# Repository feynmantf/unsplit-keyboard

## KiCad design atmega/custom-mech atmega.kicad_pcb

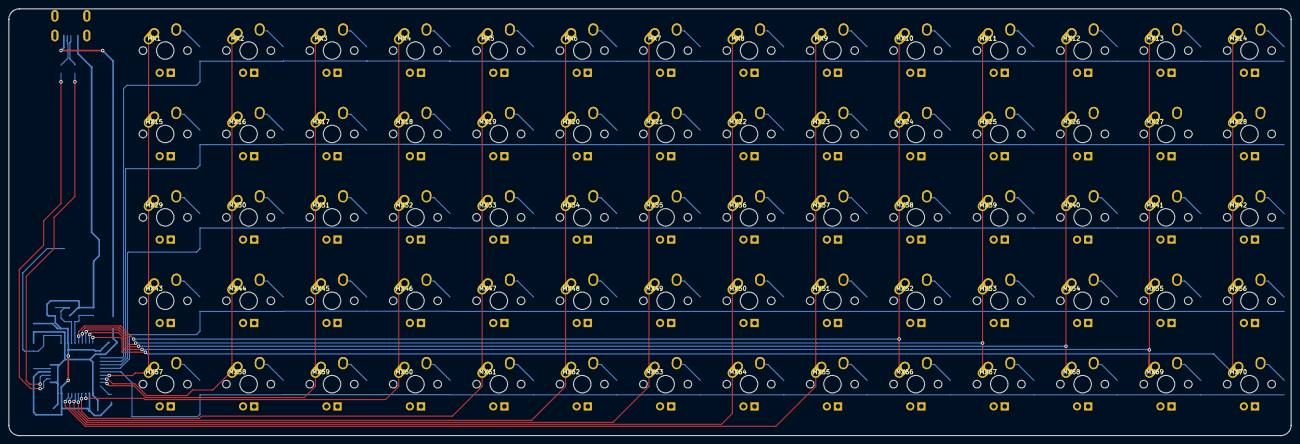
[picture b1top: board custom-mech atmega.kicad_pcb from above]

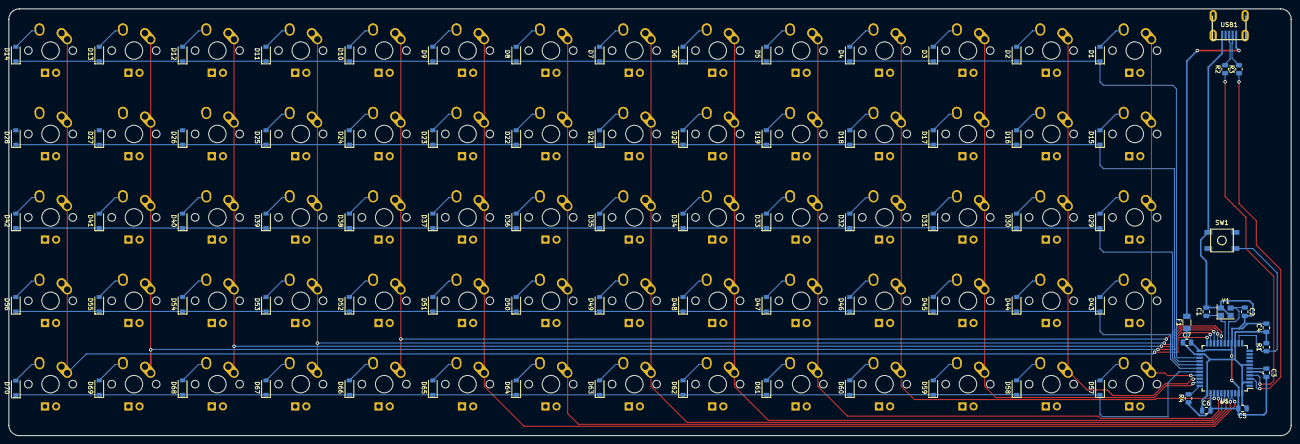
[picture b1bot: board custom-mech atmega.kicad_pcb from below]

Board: 2 copper layers, 292.9 x 97.5 mm, 156 parts (86 on the bottom side), 101 nets.

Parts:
C1, C2: 22pF; C_0805_2012Metric
C3: 1uF; C_0805_2012Metric
C4, C5, C6: 0.1uF; C_0805_2012Metric
C7: 10uF; C_0805_2012Metric
D1, D2, D3, D4, D5, D6, D7, D8, D9, D10, D11, D12, D13, D14, D15, D16, D17, D18, D19, D20, D21, D22, D23, D24, D25, D26, D27, D28, D29, D30, D31, D32, D33, D34, D35, D36, D37, D38, D39, D40, D41, D42, D43, D44, D45, D46, D47, D48, D49, D50, D51, D52, D53, D54, D55, D56, D57, D58, D59, D60, D61, D62, D63, D64, D65, D66, D67, D68, D69, D70: SOD-123; D_SOD-123
F1: 500mA; Fuse_1206_3216Metric
MX1, MX2, MX3, MX4, MX5, MX6, MX7, MX8, MX9, MX10, MX11, MX12, MX13, MX14, MX15, MX16, MX17, MX18, MX19, MX20, MX21, MX22, MX23, MX24, MX25, MX26, MX27, MX28, MX29, MX30, MX31, MX32, MX33, MX34, MX35, MX36, MX37, MX38, MX39, MX40, MX41, MX42, MX43, MX44, MX45, MX46, MX47, MX48, MX49, MX50, MX51, MX52, MX53, MX54, MX55, MX56, MX57, MX58, MX59, MX60, MX61, MX62, MX63, MX64, MX65, MX66, MX67, MX68, MX69, MX70: MX-NoLED; MX-1U
R1, R4: 10k; R_0805_2012Metric
R2, R3: 22; R_0805_2012Metric
SW1: SW_Push; SKQG-1155865
U1: ATmega32U4-AU; TQFP-44_10x10mm_P0.8mm
USB1: Molex-0548190589
Y1: 16MHz; Crystal_SMD_3225-4Pin_3.2x2.5mm

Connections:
+5V: C4.1, C5.1, C6.1, C7.1, F1.1, R1.2, U1.2, U1.7, U1.14, U1.24, U1.34, U1.44
COL0: MX1.1, MX15.1, MX29.1, MX43.1, MX57.1, U1.30
COL1: MX2.1, MX16.1, MX30.1, MX44.1, MX58.1, U1.31
COL2: MX3.1, MX17.1, MX31.1, MX45.1, MX59.1, U1.32
COL3: MX4.1, MX18.1, MX32.1, MX46.1, MX60.1, U1.36
COL4: MX5.1, MX19.1, MX33.1, MX47.1, MX61.1, U1.37
COL5: MX6.1, MX20.1, MX34.1, MX48.1, MX62.1, U1.38
COL6: MX7.1, MX21.1, MX35.1, MX49.1, MX63.1, U1.39
COL7: MX8.1, MX22.1, MX36.1, MX50.1, MX64.1, U1.40
COL8: MX9.1, MX23.1, MX37.1, MX51.1, MX65.1, U1.41
COL9: MX10.1, MX24.1, MX38.1, MX52.1, MX66.1, U1.18
COL10: MX11.1, MX25.1, MX39.1, MX53.1, MX67.1, U1.19
COL11: MX12.1, MX26.1, MX40.1, MX54.1, MX68.1, U1.20
COL12: MX13.1, MX27.1, MX41.1, MX55.1, MX69.1, U1.21
COL13: MX14.1, MX28.1, MX42.1, MX56.1, MX70.1, U1.22
D+: R2.2, USB1.3
D-: R3.2, USB1.4
GND: C1.2, C2.2, C3.2, C4.2, C5.2, C6.2, C7.2, R4.1, SW1.1, U1.5, U1.15, U1.23, U1.35, U1.43, USB1.1, Y1.2, Y1.4
unnamed: C1.1, U1.17, Y1.1
unnamed: C2.1, U1.16, Y1.3
unnamed: C3.1, U1.6
unnamed: D1.2, MX1.2
unnamed: D2.2, MX2.2
unnamed: D3.2, MX3.2
unnamed: D4.2, MX4.2
unnamed: D5.2, MX5.2
unnamed: D6.2, MX6.2
unnamed: D7.2, MX7.2
unnamed: D8.2, MX8.2
unnamed: D9.2, MX9.2
unnamed: D10.2, MX10.2
unnamed: D11.2, MX11.2
unnamed: D12.2, MX12.2
unnamed: D13.2, MX13.2
unnamed: D14.2, MX14.2
unnamed: D15.2, MX15.2
unnamed: D16.2, MX16.2
unnamed: D17.2, MX17.2
unnamed: D18.2, MX18.2
unnamed: D19.2, MX19.2
unnamed: D20.2, MX20.2
unnamed: D21.2, MX21.2
unnamed: D22.2, MX22.2
unnamed: D23.2, MX23.2
unnamed: D24.2, MX24.2
unnamed: D25.2, MX25.2
unnamed: D26.2, MX26.2
unnamed: D27.2, MX27.2
unnamed: D28.2, MX28.2
unnamed: D29.2, MX29.2
unnamed: D30.2, MX30.2
unnamed: D31.2, MX31.2
unnamed: D32.2, MX32.2
unnamed: D33.2, MX33.2
unnamed: D34.2, MX34.2
unnamed: D35.2, MX35.2
unnamed: D36.2, MX36.2
unnamed: D37.2, MX37.2
unnamed: D38.2, MX38.2
unnamed: D39.2, MX39.2
unnamed: D40.2, MX40.2
unnamed: D41.2, MX41.2
unnamed: D42.2, MX42.2
unnamed: D43.2, MX43.2
unnamed: D44.2, MX44.2
unnamed: D45.2, MX45.2
unnamed: D46.2, MX46.2
unnamed: D47.2, MX47.2
unnamed: D48.2, MX48.2
unnamed: D49.2, MX49.2
unnamed: D50.2, MX50.2
unnamed: D51.2, MX51.2
unnamed: D52.2, MX52.2
unnamed: D53.2, MX53.2
unnamed: D54.2, MX54.2
unnamed: D55.2, MX55.2
unnamed: D56.2, MX56.2
unnamed: D57.2, MX57.2
unnamed: D58.2, MX58.2
unnamed: D59.2, MX59.2
unnamed: D60.2, MX60.2
unnamed: D61.2, MX61.2
unnamed: D62.2, MX62.2
unnamed: D63.2, MX63.2
unnamed: D64.2, MX64.2
unnamed: D65.2, MX65.2
unnamed: D66.2, MX66.2
unnamed: D67.2, MX67.2
unnamed: D68.2, MX68.2
unnamed: D69.2, MX69.2
unnamed: D70.2, MX70.2
unnamed: R1.1, SW1.2, U1.13
unnamed: R2.1, U1.4
unnamed: R3.1, U1.3
unnamed: R4.2, U1.33
ROW0: D1.1, D2.1, D3.1, D4.1, D5.1, D6.1, D7.1, D8.1, D9.1, D10.1, D11.1, D12.1, D13.1, D14.1, U1.25
ROW1: D15.1, D16.1, D17.1, D18.1, D19.1, D20.1, D21.1, D22.1, D23.1, D24.1, D25.1, D26.1, D27.1, D28.1, U1.26
ROW2: D29.1, D30.1, D31.1, D32.1, D33.1, D34.1, D35.1, D36.1, D37.1, D38.1, D39.1, D40.1, D41.1, D42.1, U1.27
ROW3: D43.1, D44.1, D45.1, D46.1, D47.1, D48.1, D49.1, D50.1, D51.1, D52.1, D53.1, D54.1, D55.1, D56.1, U1.28
ROW4: D57.1, D58.1, D59.1, D60.1, D61.1, D62.1, D63.1, D64.1, D65.1, D66.1, D67.1, D68.1, D69.1, D70.1, U1.29
VCC: F1.2, USB1.5

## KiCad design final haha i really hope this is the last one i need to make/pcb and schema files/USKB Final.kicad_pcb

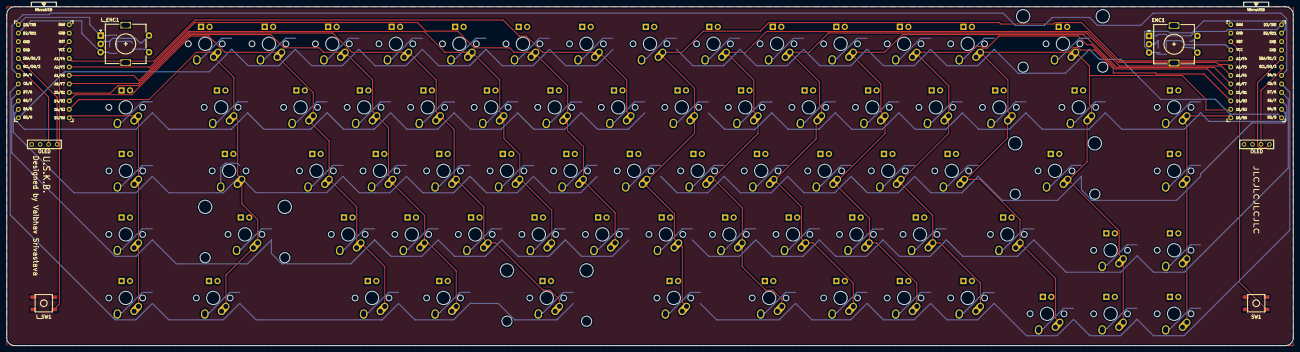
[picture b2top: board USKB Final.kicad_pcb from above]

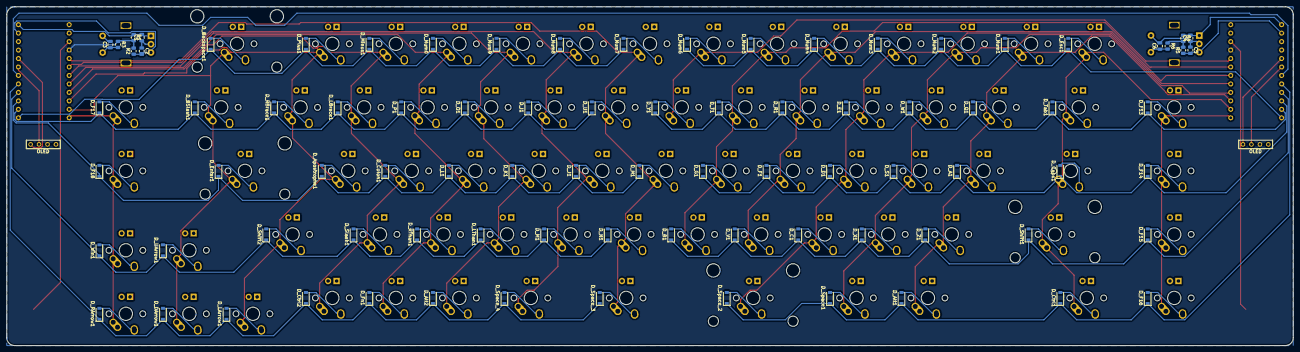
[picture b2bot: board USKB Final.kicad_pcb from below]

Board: 2 copper layers, 385.8 x 101.6 mm, 166 parts (85 on the bottom side), 114 nets.

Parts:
C1, C2, C3, C4, C5, C6: 0.1u; C_0805_2012Metric
D_A1: SMD_123; D_SOD-123
D_Alt1, D_Alt2: SMD_123; D_SOD-123
D_Apostrophe1: SMD_123; D_SOD-123
D_B1: SMD_123; D_SOD-123
D_BSlash1: SMD_123; D_SOD-123
D_Backspace1: SMD_123; D_SOD-123
D_C1: SMD_123; D_SOD-123
D_Caps1: SMD_123; D_SOD-123
D_Colon1: SMD_123; D_SOD-123
D_Ctrl1, D_Ctrl2: SMD_123; D_SOD-123
D_D1: SMD_123; D_SOD-123
D_DArrow1: SMD_123; D_SOD-123
D_E1: SMD_123; D_SOD-123
D_Enter1: SMD_123; D_SOD-123
D_Esc1: SMD_123; D_SOD-123
D_F1, D_F13, D_F14, D_F15, D_F16, D_F17, D_F18: SMD_123; D_SOD-123
D_Fn1: SMD_123; D_SOD-123
D_G1: SMD_123; D_SOD-123
D_H1: SMD_123; D_SOD-123
D_I1: SMD_123; D_SOD-123
D_J1: SMD_123; D_SOD-123
D_K1: SMD_123; D_SOD-123
D_L1: SMD_123; D_SOD-123
D_LArrow1: SMD_123; D_SOD-123
D_LBrace1: SMD_123; D_SOD-123
D_LThan1: SMD_123; D_SOD-123
D_M1: SMD_123; D_SOD-123
D_Minus1: SMD_123; D_SOD-123
D_N1: SMD_123; D_SOD-123
D_Num0, D_Num1, D_Num2, D_Num3, D_Num4, D_Num5, D_Num6, D_Num7, D_Num8, D_Num9: SMD_123; D_SOD-123
D_O1: SMD_123; D_SOD-123
D_P1: SMD_123; D_SOD-123
D_Plus1: SMD_123; D_SOD-123
D_Q1: SMD_123; D_SOD-123
D_R1: SMD_123; D_SOD-123
D_RArrow1: SMD_123; D_SOD-123
D_RBrace1: SMD_123; D_SOD-123
D_RThan1: SMD_123; D_SOD-123
D_S1: SMD_123; D_SOD-123
D_Shift1, D_Shift2: SMD_123; D_SOD-123
D_Slash1: SMD_123; D_SOD-123
D_Space1: SMD_123; D_SOD-123
D_Space_2, D_Space_3, D_Space_4: SMD_123; D_SOD-123
D_T1: SMD_123; D_SOD-123
D_Tab1: SMD_123; D_SOD-123
D_U1: SMD_123; D_SOD-123
D_UArrow1: SMD_123; D_SOD-123
D_V1: SMD_123; D_SOD-123
D_W1: SMD_123; D_SOD-123
D_Win1: SMD_123; D_SOD-123
D_X1: SMD_123; D_SOD-123
D_Y1: SMD_123; D_SOD-123
D_Z1: SMD_123; D_SOD-123
ENC1: Rotary_Encoder_Switch; RotaryEncoder_Alps_EC11E-Switch_Vertical_H20mm
K_A1: MX-NoLED; MX-1U
K_Alt1: MX-NoLED; MX-1.25U
K_Alt2: MX-NoLED; MX-1U
K_Apostrophe1: MX-NoLED; MX-1U
K_B1: MX-NoLED; MX-1U
K_BSlash1: MX-NoLED; MX-1.5U
K_Backspace1: MX-NoLED; MX-2U
K_C1: MX-NoLED; MX-1U
K_Caps1: MX-NoLED; MX-1.75U
K_Colon1: MX-NoLED; MX-1U
K_Ctrl1: MX-NoLED; MX-1.25U
K_Ctrl2: MX-NoLED; MX-1U
K_D1: MX-NoLED; MX-1U
K_DArrow1: MX-NoLED; MX-1U
K_E1: MX-NoLED; MX-1U
K_Enter1: MX-NoLED; MX-2.25U
K_Esc1: MX-NoLED; MX-1U
K_F1, K_F13, K_F14, K_F15, K_F16, K_F17, K_F18: MX-NoLED; MX-1U
K_Fn1: MX-NoLED; MX-1U
K_G1: MX-NoLED; MX-1U
K_H1: MX-NoLED; MX-1U
K_I1: MX-NoLED; MX-1U
K_J1: MX-NoLED; MX-1U
K_K1: MX-NoLED; MX-1U
K_L1: MX-NoLED; MX-1U
K_LArrow1: MX-NoLED; MX-1U
K_LBrace1: MX-NoLED; MX-1U
K_LThan1: MX-NoLED; MX-1U
K_M1: MX-NoLED; MX-1U
K_Minus1: MX-NoLED; MX-1U
K_N1: MX-NoLED; MX-1U
K_Num0, K_Num1, K_Num2, K_Num3, K_Num4, K_Num5, K_Num6, K_Num7, K_Num8, K_Num9: MX-NoLED; MX-1U
K_O1: MX-NoLED; MX-1U
K_P1: MX-NoLED; MX-1U
K_Plus1: MX-NoLED; MX-1U
K_Q1: MX-NoLED; MX-1U
K_R1: MX-NoLED; MX-1U
K_RArrow1: MX-NoLED; MX-1U
K_RBrace1: MX-NoLED; MX-1U
K_RThan1: MX-NoLED; MX-1U
K_S1: MX-NoLED; MX-1U
K_Shift1: MX-NoLED; MX-2.25U
K_Shift2: MX-NoLED; MX-1.75U
K_Slash1: MX-NoLED; MX-1U
K_Space1: MX-NoLED; MX-1U
K_Space_2: MX-NoLED; MX-2.25U
K_Space_3: MX-NoLED; MX-1.75U
K_Space_4: MX-NoLED; MX-1.25U
K_T1: MX-NoLED; MX-1U
K_Tab1: MX-NoLED; MX-1.5U
K_U1: MX-NoLED; MX-1U
K_UArrow1: MX-NoLED; MX-1U
K_V1: MX-NoLED; MX-1U
K_W1: MX-NoLED; MX-1U
K_Win1: MX-NoLED; MX-1U
K_X1: MX-NoLED; MX-1U
K_Y1: MX-NoLED; MX-1U
K_Z1: MX-NoLED; MX-1U
L_ENC1: Rotary_Encoder_Switch; RotaryEncoder_Alps_EC11E-Switch_Vertical_H20mm
L_OL1: OLED
L_SW1: SW_PUSH; SKQG-1155865
L_U1: ProMicro; ProMicro_v3
OL1: OLED
R1, R2, R3, R4, R5, R6: 10k; R_0805_2012Metric
SW1: SW_PUSH; SKQG-1155865
U1: ProMicro; ProMicro_v3

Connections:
COL0: K_H1.1, K_N1.1, K_Num7.1, K_Space_3.1, K_U1.1, U1.20
COL1: K_I1.1, K_J1.1, K_M1.1, K_Num8.1, K_Space_4.1, U1.19
COL2: K_Alt2.1, K_K1.1, K_LThan1.1, K_Num9.1, K_O1.1, U1.18
COL3: K_Fn1.1, K_L1.1, K_Num0.1, K_P1.1, K_RThan1.1, U1.17
COL4: K_Colon1.1, K_Ctrl2.1, K_LBrace1.1, K_Minus1.1, K_Slash1.1, U1.16
COL5: K_Apostrophe1.1, K_LArrow1.1, K_Plus1.1, K_RBrace1.1, K_Shift2.1, U1.15
COL6: K_BSlash1.1, K_Backspace1.1, K_DArrow1.1, K_Enter1.1, K_UArrow1.1, U1.14
COL7: K_F17.1, K_F18.1, K_RArrow1.1, K_Win1.1, U1.13
DATA: L_U1.7, U1.7
GND: C1.1, C2.1, C3.2, C4.1, C5.1, C6.2, ENC1.C, ENC1.S2, L_ENC1.C, L_ENC1.S2, L_OL1.4, L_SW1.2, L_U1.3, L_U1.4, L_U1.23, OL1.4, SW1.2, U1.3, U1.4, U1.23
K_ENC: C3.1, ENC1.S1, R3.2
L_COL0: K_F13.1, K_F14.1, K_F15.1, K_F16.1, L_U1.13
L_COL1: K_Caps1.1, K_Ctrl1.1, K_Esc1.1, K_Shift1.1, K_Tab1.1, L_U1.14
L_COL2: K_A1.1, K_Alt1.1, K_Num1.1, K_Q1.1, K_Z1.1, L_U1.15
L_COL3: K_Num2.1, K_S1.1, K_Space1.1, K_W1.1, K_X1.1, L_U1.16
L_COL4: K_C1.1, K_D1.1, K_E1.1, K_Num3.1, K_Space_2.1, L_U1.17
L_COL5: K_F1.1, K_Num4.1, K_R1.1, K_V1.1, L_U1.18
L_COL6: K_B1.1, K_G1.1, K_Num5.1, K_T1.1, L_U1.19
L_COL7: K_Num6.1, K_Y1.1, L_U1.20
L_K_ENC: C6.1, L_ENC1.S1, R6.2
L_RESET: L_SW1.1, L_U1.22
L_ROT_A: C4.2, L_ENC1.A, L_U1.1, R4.1
L_ROT_B: C5.2, L_ENC1.B, L_U1.2, R5.1
L_ROW0: D_Esc1.1, D_Num1.1, D_Num2.1, D_Num3.1, D_Num4.1, D_Num5.1, D_Num6.1, L_U1.12
L_ROW1: D_E1.1, D_F13.1, D_Q1.1, D_R1.1, D_T1.1, D_Tab1.1, D_W1.1, D_Y1.1, L_U1.11
L_ROW2: D_A1.1, D_Caps1.1, D_D1.1, D_F1.1, D_F14.1, D_G1.1, D_S1.1, L_U1.10
L_ROW3: D_B1.1, D_C1.1, D_F15.1, D_Shift1.1, D_V1.1, D_X1.1, D_Z1.1, L_U1.9
L_ROW4: D_Alt1.1, D_Ctrl1.1, D_F16.1, D_Space1.1, D_Space_2.1, L_U1.8
L_SCL: L_OL1.2, L_U1.6
L_SDA: L_OL1.1, L_U1.5
unnamed: D_A1.2, K_A1.2
unnamed: D_Alt1.2, K_Alt1.2
unnamed: D_Alt2.2, K_Alt2.2
unnamed: D_Apostrophe1.2, K_Apostrophe1.2
unnamed: D_B1.2, K_B1.2
unnamed: D_BSlash1.2, K_BSlash1.2
unnamed: D_Backspace1.2, K_Backspace1.2
unnamed: D_C1.2, K_C1.2
unnamed: D_Caps1.2, K_Caps1.2
unnamed: D_Colon1.2, K_Colon1.2
unnamed: D_Ctrl1.2, K_Ctrl1.2
unnamed: D_Ctrl2.2, K_Ctrl2.2
unnamed: D_D1.2, K_D1.2
unnamed: D_DArrow1.2, K_DArrow1.2
unnamed: D_E1.2, K_E1.2
unnamed: D_Enter1.2, K_Enter1.2
unnamed: D_Esc1.2, K_Esc1.2
unnamed: D_F1.2, K_F1.2
unnamed: D_F13.2, K_F13.2
unnamed: D_F14.2, K_F14.2
unnamed: D_F15.2, K_F15.2
unnamed: D_F16.2, K_F16.2
unnamed: D_F17.2, K_F17.2
unnamed: D_F18.2, K_F18.2
unnamed: D_Fn1.2, K_Fn1.2
unnamed: D_G1.2, K_G1.2
unnamed: D_H1.2, K_H1.2
unnamed: D_I1.2, K_I1.2
unnamed: D_J1.2, K_J1.2
unnamed: D_K1.2, K_K1.2
unnamed: D_L1.2, K_L1.2
unnamed: D_LArrow1.2, K_LArrow1.2
unnamed: D_LBrace1.2, K_LBrace1.2
unnamed: D_LThan1.2, K_LThan1.2
unnamed: D_M1.2, K_M1.2
unnamed: D_Minus1.2, K_Minus1.2
unnamed: D_N1.2, K_N1.2
unnamed: D_Num0.2, K_Num0.2
unnamed: D_Num1.2, K_Num1.2
unnamed: D_Num2.2, K_Num2.2
unnamed: D_Num3.2, K_Num3.2
unnamed: D_Num4.2, K_Num4.2
unnamed: D_Num5.2, K_Num5.2
unnamed: D_Num6.2, K_Num6.2
unnamed: D_Num7.2, K_Num7.2
unnamed: D_Num8.2, K_Num8.2
unnamed: D_Num9.2, K_Num9.2
unnamed: D_O1.2, K_O1.2
unnamed: D_P1.2, K_P1.2
unnamed: D_Plus1.2, K_Plus1.2
unnamed: D_Q1.2, K_Q1.2
unnamed: D_R1.2, K_R1.2
unnamed: D_RArrow1.2, K_RArrow1.2
unnamed: D_RBrace1.2, K_RBrace1.2
unnamed: D_RThan1.2, K_RThan1.2
unnamed: D_S1.2, K_S1.2
unnamed: D_Shift1.2, K_Shift1.2
unnamed: D_Shift2.2, K_Shift2.2
unnamed: D_Slash1.2, K_Slash1.2
unnamed: D_Space1.2, K_Space1.2
unnamed: D_Space_2.2, K_Space_2.2
unnamed: D_Space_3.2, K_Space_3.2
unnamed: D_Space_4.2, K_Space_4.2
unnamed: D_T1.2, K_T1.2
unnamed: D_Tab1.2, K_Tab1.2
unnamed: D_U1.2, K_U1.2
unnamed: D_UArrow1.2, K_UArrow1.2
unnamed: D_V1.2, K_V1.2
unnamed: D_W1.2, K_W1.2
unnamed: D_Win1.2, K_Win1.2
unnamed: D_X1.2, K_X1.2
unnamed: D_Y1.2, K_Y1.2
unnamed: D_Z1.2, K_Z1.2
RESET: SW1.1, U1.22
ROT_A: C1.2, ENC1.A, R1.1, U1.1
ROT_B: C2.2, ENC1.B, R2.1, U1.2
ROW0: D_Backspace1.1, D_Minus1.1, D_Num0.1, D_Num7.1, D_Num8.1, D_Num9.1, D_Plus1.1, U1.12
ROW1: D_BSlash1.1, D_F17.1, D_I1.1, D_LBrace1.1, D_O1.1, D_P1.1, D_RBrace1.1, D_U1.1, U1.11
ROW2: D_Apostrophe1.1, D_Colon1.1, D_Enter1.1, D_F18.1, D_H1.1, D_J1.1, D_K1.1, D_L1.1, U1.10
ROW3: D_LThan1.1, D_M1.1, D_N1.1, D_RThan1.1, D_Shift2.1, D_Slash1.1, D_UArrow1.1, D_Win1.1, U1.9
ROW4: D_Alt2.1, D_Ctrl2.1, D_DArrow1.1, D_Fn1.1, D_LArrow1.1, D_RArrow1.1, D_Space_3.1, D_Space_4.1, U1.8
SCL: OL1.2, U1.6
SDA: OL1.1, U1.5
VCC: L_OL1.3, L_U1.21, OL1.3, R1.2, R2.2, R3.1, R4.2, R5.2, R6.1, U1.21
